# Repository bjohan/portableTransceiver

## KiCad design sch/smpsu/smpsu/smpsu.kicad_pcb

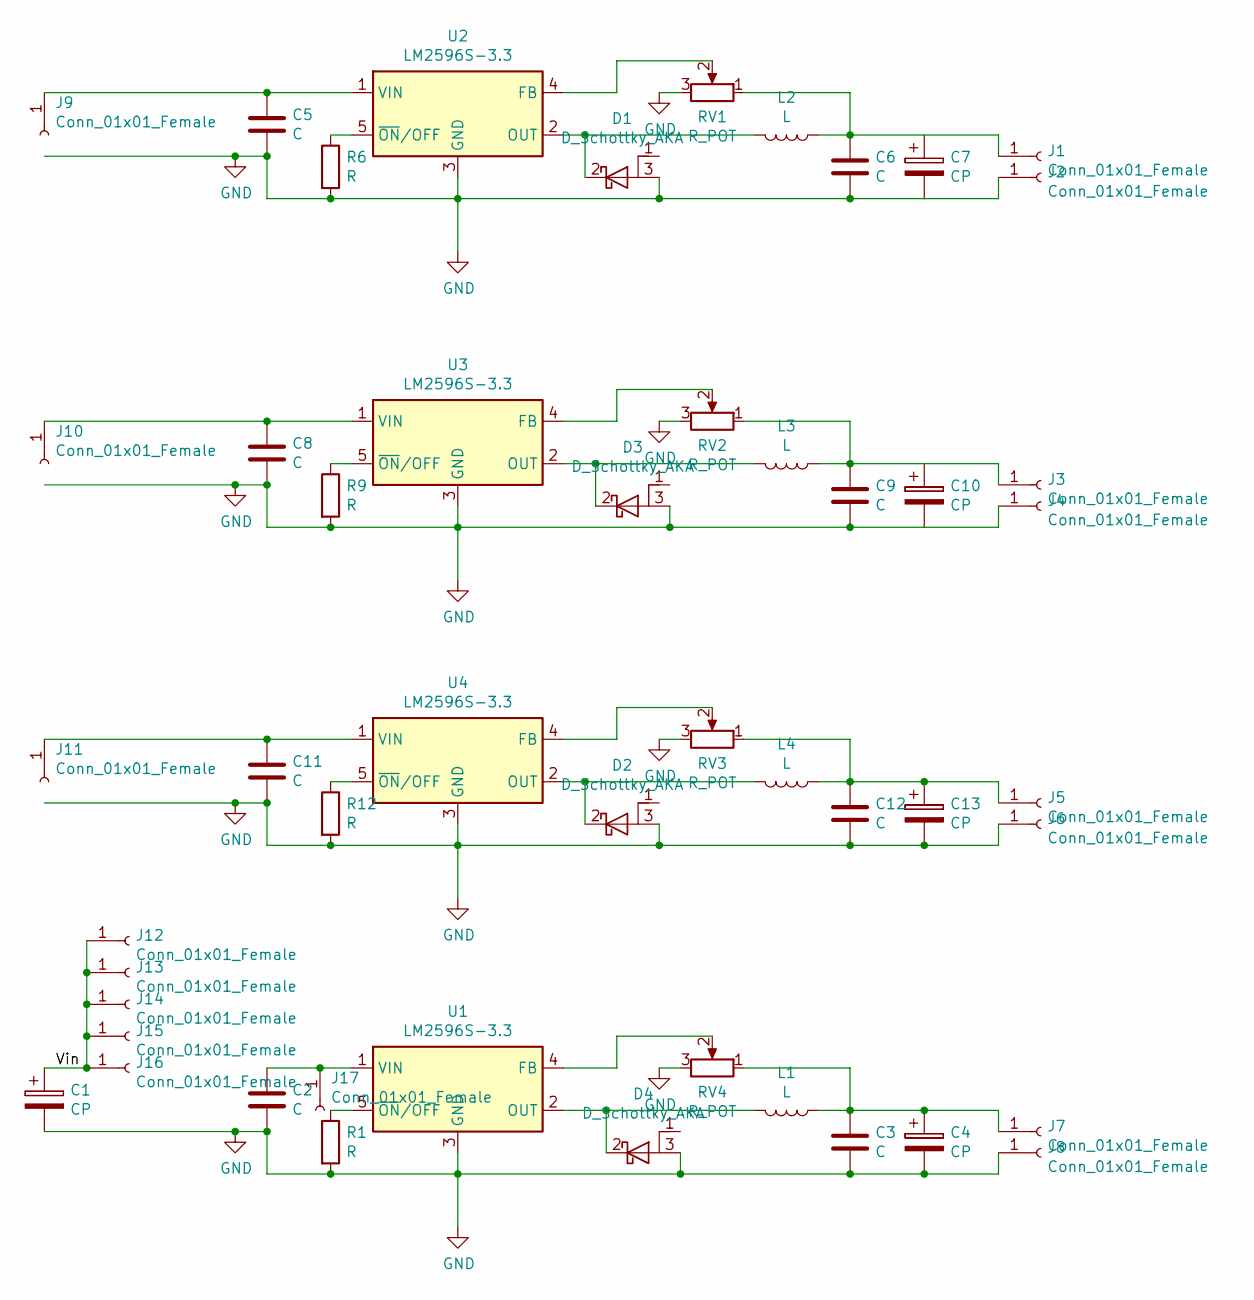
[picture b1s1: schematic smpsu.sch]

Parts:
C1: CP; CP_Radial_D18.0mm_P7.50mm
C2, C3, C5, C6, C8, C9, C11, C12: C; R_0805_HandSoldering
C4, C7, C10, C13: CP; CP_Radial_D10.0mm_P3.50mm
D1, D2, D3, D4: D_Schottky_AKA; TO-220-3_Vertical
J1, J2, J3, J4, J5, J6, J7, J8, J9, J10, J11, J12, J13, J14, J15, J16, J17: Conn_01x01_Female; SolderWirePad_single_0-8mmDrill
L1, L2, L3, L4: L; Choke_Toroid_12x16mm_Vertical
R1, R6, R9, R12: R; R_0805_HandSoldering
RV1, RV2, RV3, RV4: R_POT; Potentiometer_Trimmer_Bourns_3214J
U1, U2, U3, U4: LM2596S-3.3; TO-263-5_TabPin3

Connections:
/Vin: C1.1, J12.1, J13.1, J14.1, J15.1, J16.1
GND: C1.2, C2.2, C3.2, C4.2, C5.2, C6.2, C7.2, C8.2, C9.2, C10.2, C11.2, C12.2, C13.2, D1.3 (A), D2.3 (A), D3.3 (A), D4.3 (A), J2.1, J4.1, J6.1, J8.1, R1.2, R6.2, R9.2, R12.2, RV1.3, RV2.3, RV3.3, RV4.3, U1.3 (GND), U2.3 (GND), U3.3 (GND), U4.3 (GND)
unnamed: C2.1, J17.1, U1.1 (VIN)
unnamed: C3.1, C4.1, J7.1, L1.1, RV4.1
unnamed: C5.1, J9.1, U2.1 (VIN)
unnamed: C6.1, C7.1, J1.1, L2.1, RV1.1
unnamed: C8.1, J10.1, U3.1 (VIN)
unnamed: C9.1, C10.1, J3.1, L3.1, RV2.1
unnamed: C11.1, J11.1, U4.1 (VIN)
unnamed: C12.1, C13.1, J5.1, L4.1, RV3.1
unnamed: D1.2 (K), L2.2, U2.2 (OUT)
unnamed: D2.2 (K), L4.2, U4.2 (OUT)
unnamed: D3.2 (K), L3.2, U3.2 (OUT)
unnamed: D4.2 (K), L1.2, U1.2 (OUT)
unnamed: R1.1, U1.5 (~ON~/OFF)
unnamed: R6.1, U2.5 (~ON~/OFF)
unnamed: R9.1, U3.5 (~ON~/OFF)
unnamed: R12.1, U4.5 (~ON~/OFF)
unnamed: RV1.2, U2.4 (FB)
unnamed: RV2.2, U3.4 (FB)
unnamed: RV3.2, U4.4 (FB)
unnamed: RV4.2, U1.4 (FB)

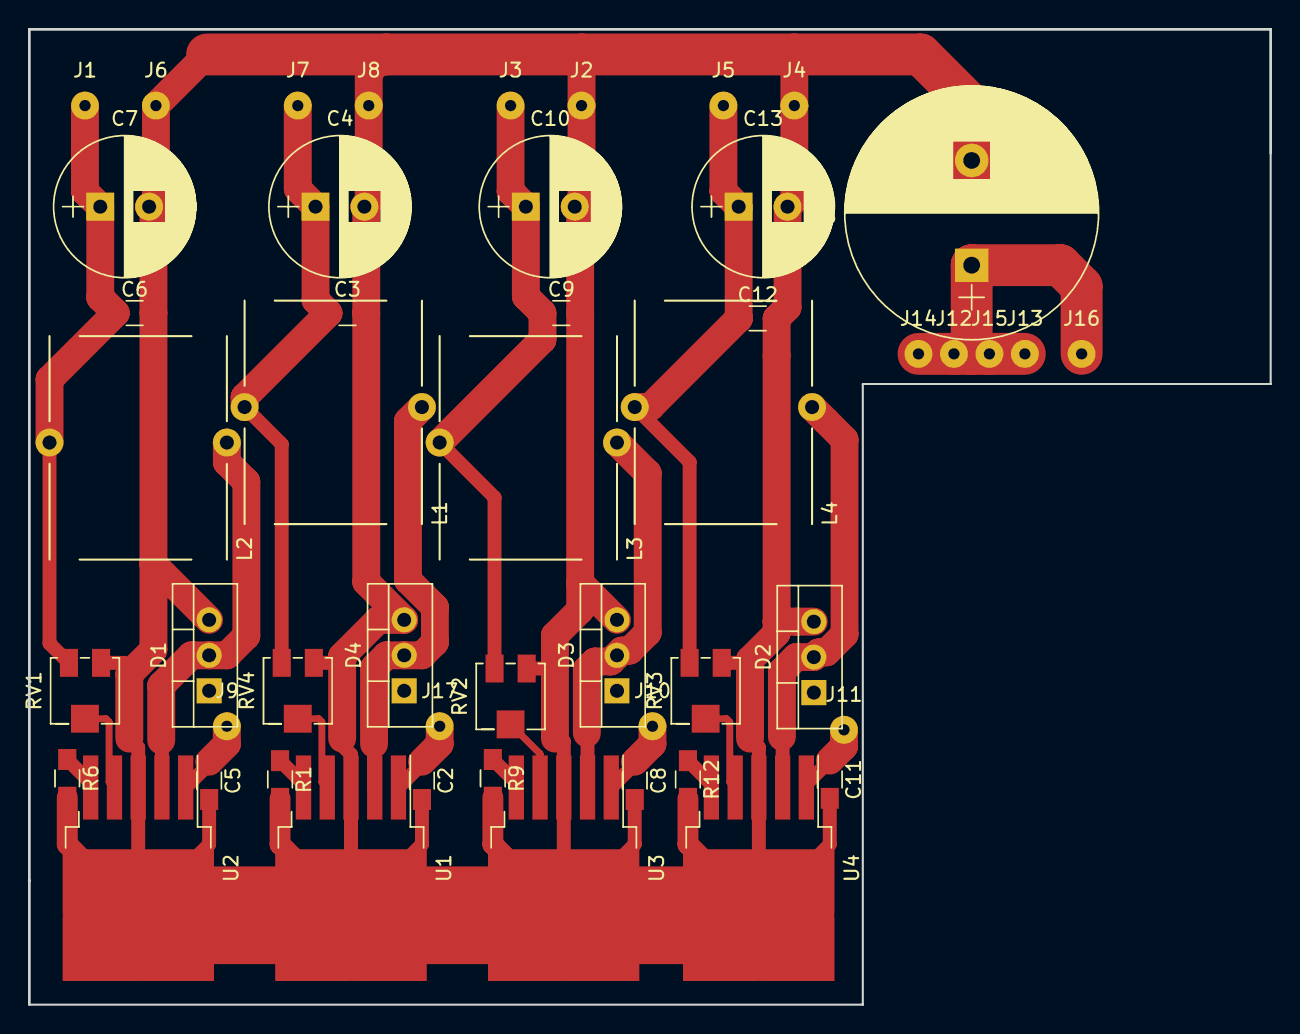
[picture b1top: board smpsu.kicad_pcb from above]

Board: 2 copper layers, 88.9 x 69.9 mm, 50 parts (0 on the bottom side), 22 nets.

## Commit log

2019-06-06 Added openscad files for most mecanical parts
2019-06-06 more
2019-06-07 First version of switch mode psu/emi generator
2019-06-07 Updated scad model with pcb for size
2022-04-17 mechanics for preselector
2022-04-17 restored some code that hade gone awol
2022-12-11 Added scad files
2022-12-11 Updated library
2023-03-26 Added some 3d models and updated scad files
2023-03-26 Added some measurement data
2023-05-20 Started adding measurements and fixing structure
2023-05-20 Added mixer measurements
2023-05-20 Added smpsu test schematic and gerbers
2023-05-20 old simulation results
2023-05-20 Updated submodule
2023-05-20 Added gitignore
2023-05-20 Started writing code for converter
2023-05-21 Started some leveling experimetns with the frequency converter block
2023-05-21 Started measuring
2023-05-25 Added some measurements done on leveleing
2024-03-02 Added measurement data
2024-03-02 Added updated scad files
